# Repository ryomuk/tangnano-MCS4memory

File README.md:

# tangnano-MCS4memory
Memory system for Intel 4004 using Tang Nano 20K

This document is written mostly in Japanese.
If necessary, please use a translation service such as DeepL (I recommend this) or Google.

## 概要
[emu8080on4004](https://github.com/ryomuk/emu8080on4004)を動作させるための4004実験ボード(Rev.2.1)の「4004以外の部分」(主にメモリシステム)をTang Nano 20K に実装しました．
これにより，DigikeyやMouserで入手可能な部品とTangNano20KだけでIntel4004を動作させることができます．

## ボードの構成

部品のほとんどはレベル変換用IC(15V←→3.3V, 15Vクロックドライバ, UART用5V耐圧バッファ)です．

## Tang Nano 20Kに実装したもの
- 4002 x 4個 (data ram, 出力ポート)．出力ポートのLEDはRAM0の4個のみ．
- 4289 のプログラムメモリへのアクセス機能(ポート機能は未実装)
- プログラム領域のROM (4KB)
- プログラム領域のRAM (256byte x 256バンク = 64KB)
- 2相クロックジェネレータ

Rev.2.1ボードにおける下記の赤枠の部分がTangNano20Kに実装されています．

## 電源について
一般に，4004の回路は「VSS=-15V, VDD=0V(GND)」もしくは，「VSS=-10V, VDD=+5V, GND=0V」で設計されることが多いですが，3.3VCMOSへのレベル変換を考えた場合，
「VSS=+15V, VDD=0V(GND)」とした方が扱いやすそうだったのでそのようにしています．
(ちなみに，15V系CMOSはVSSとVDDは4004と逆で「VSS=0V(GND)，VDD=+15V」です．)
- +15Vが必要なのは4004とクロック用バッファだけで，消費電流は40mA(電力0.6W)程度なので，5V→15V,1WのDC/DCコンバータの(RECOM, ROE0515S)で生成しています．
- 外部から供給する電源は5Vのみで，消費電流はTangNano(100mA程度)とあわせて250mA程度です．いわゆる普通の5V USB電源でも動作します．

## 4004実験ボード(Rev.2.1)との互換性について
- ソフトウェアはバイナリレベルで互換性があるはずです．
- 4002の出力ポートのLED(計16個)は，RAM0の4個だけTangNanoのオンボードLEDとして実装されています．
- UARTは74HC4050経由にしたので，3.3V, 5Vの両方に対応しているはずです．(動作確認済なのは5Vのみ)

## ブログ
関連する情報が書いてあるかも．
- [Intel 4004 関連記事の目次@ブログの練習](https://blog.goo.ne.jp/tk-80/e/3fa1e2972737c7b7d1b83f4e7bd648a2)

## 更新履歴
- 2023/6/14: 初版公開

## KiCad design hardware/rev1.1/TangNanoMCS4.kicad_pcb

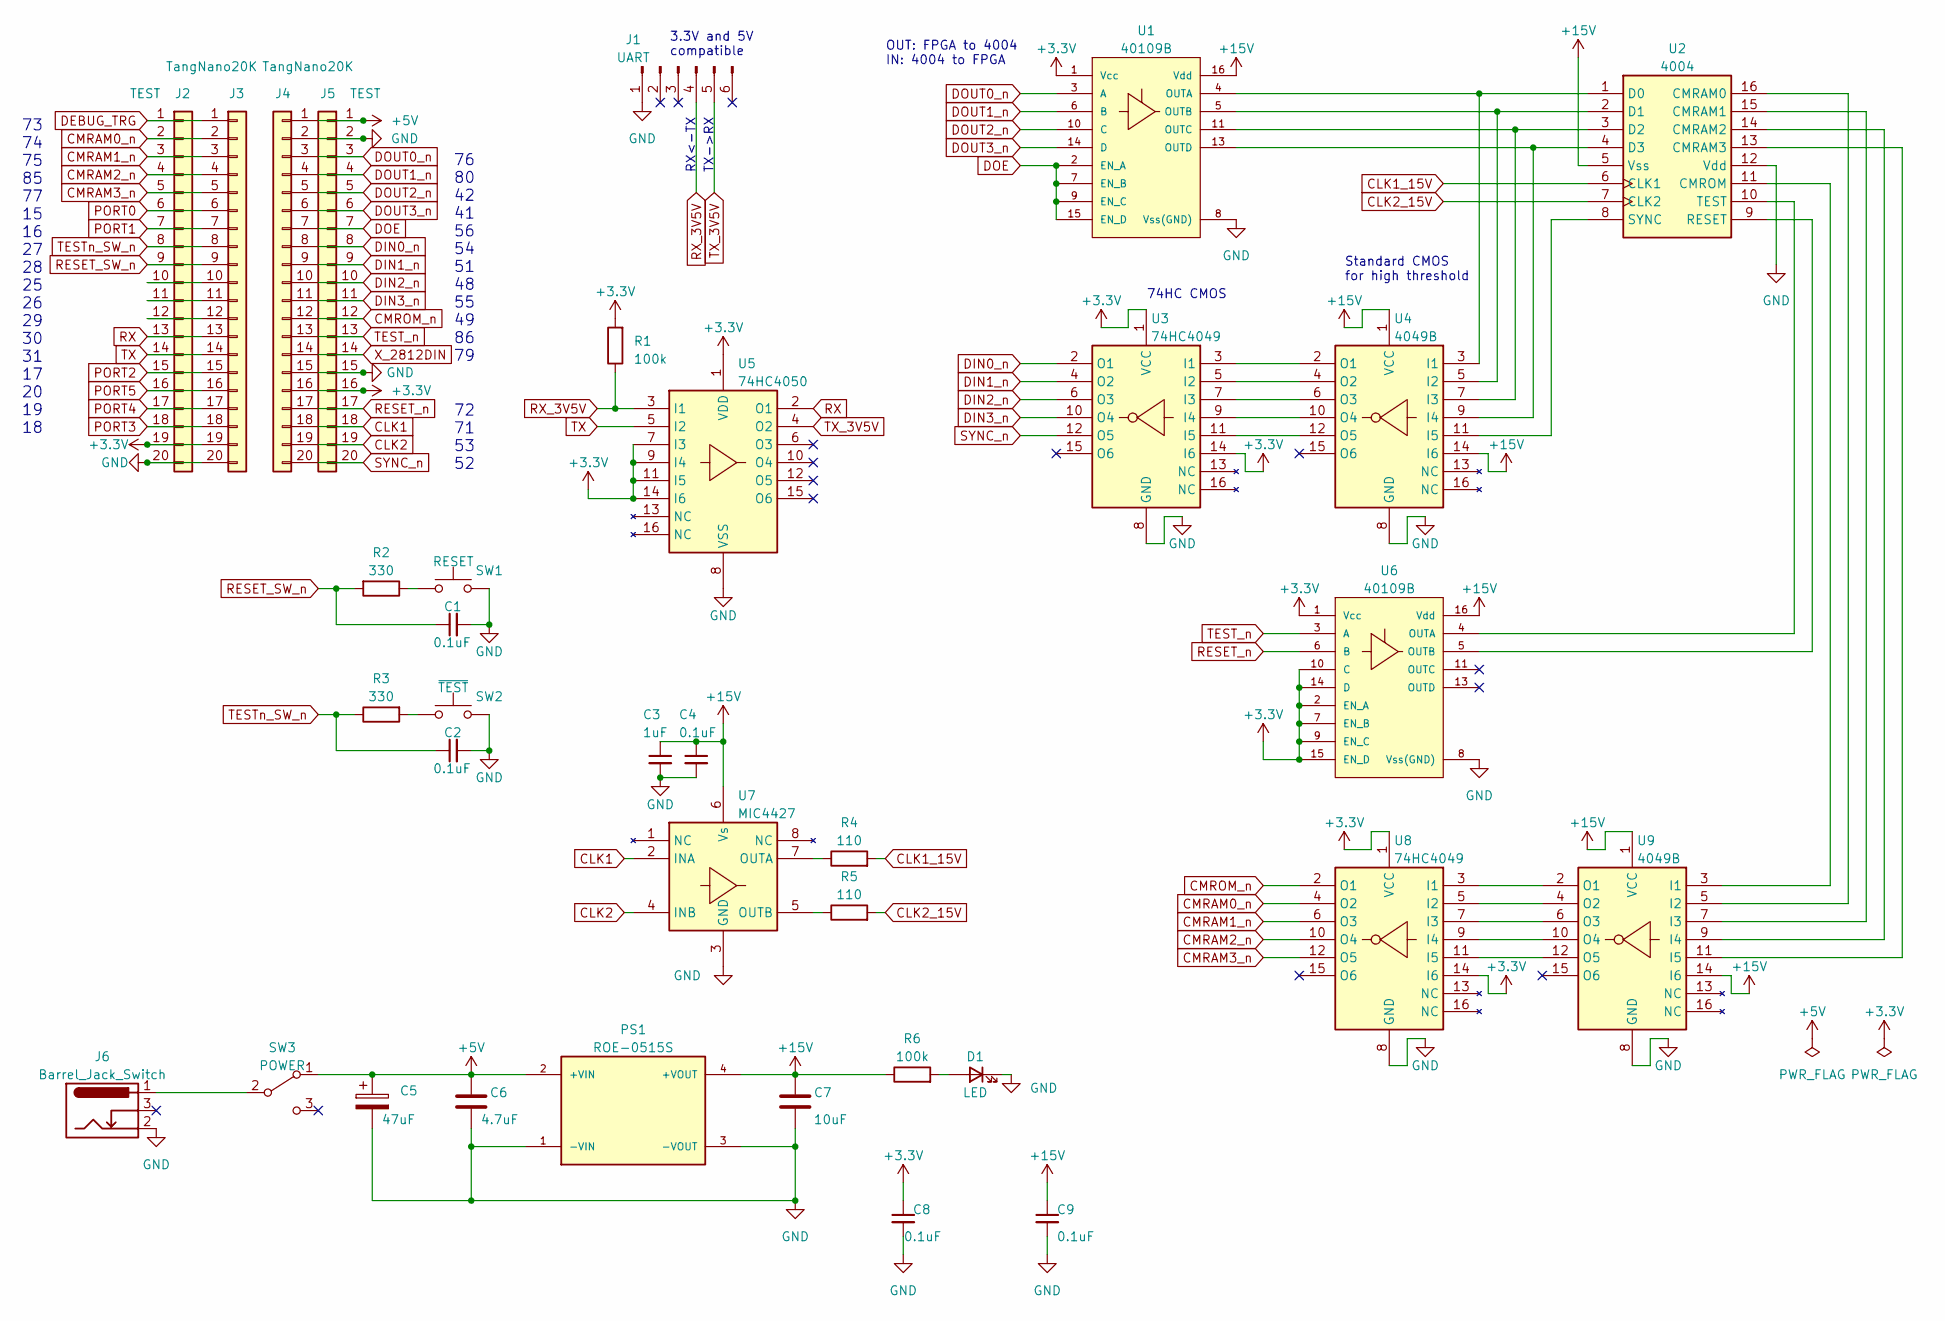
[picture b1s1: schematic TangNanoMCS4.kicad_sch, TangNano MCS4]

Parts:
C1, C2, C4, C8, C9: 0.1uF; C_Disc_D4.3mm_W1.9mm_P5.00mm
C3: 1uF; C_Disc_D4.3mm_W1.9mm_P5.00mm
C5: 47uF; CP_Radial_D6.3mm_P2.50mm
C6: 4.7uF; C_Disc_D4.7mm_W2.5mm_P5.00mm
C7: 10uF; C_Disc_D4.7mm_W2.5mm_P5.00mm
D1: LED; LED_D3.0mm
J1: UART; PinHeader_1x06_P2.54mm_Horizontal
J2, J5: TEST; PinSocket_1x20_P2.54mm_Vertical
J3, J4: TangNano20K; PinSocket_1x20_P2.54mm_Vertical
J6: Barrel_Jack_Switch; BarrelJack_Horizontal
PS1: ROE-0515S; CONV_ROE-0515S; PARTREV 5
R1, R6: 100k; R_Axial_DIN0207_L6.3mm_D2.5mm_P7.62mm_Horizontal
R2, R3: 330; R_Axial_DIN0207_L6.3mm_D2.5mm_P7.62mm_Horizontal
R4, R5: 110; R_Axial_DIN0207_L6.3mm_D2.5mm_P7.62mm_Horizontal
SW1: RESET; SW_PUSH_6mm_H4.3mm
SW2: ~{TEST}; SW_PUSH_6mm_H4.3mm
SW3: POWER; SW_SPDT_Toggle_with_mount
U1, U6: 40109B; DIP-16_W7.62mm
U2: 4004; DIP_Socket-16_W4.3_W5.08_W7.62_W10.16_W10.9_3M_216-3340-00-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
U3, U8: 74HC4049; DIP-16_W7.62mm
U4, U9: 4049B; DIP-16_W7.62mm
U5: 74HC4050; DIP-16_W7.62mm
U7: MIC4427; DIP-8_W7.62mm

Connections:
+3.3V: C8.1, J2.19, J3.19, J4.16, J5.16, R1.2, U1.1 (Vcc), U3.1 (VCC), U3.14 (I6), U5.1 (VDD), U5.7 (I3), U5.9 (I4), U5.11 (I5), U5.14 (I6), U6.1 (Vcc), U6.2 (EN_A), U6.7 (EN_B), U6.9 (EN_C), U6.10 (C), U6.14 (D), U6.15 (EN_D), U8.1 (VCC), U8.14 (I6)
+5V: C5.1, C6.1, J4.1, J5.1, PS1.2 (+VIN), SW3.1 (A)
+15V: C3.1, C4.1, C7.1, C9.1, PS1.4 (+VOUT), R6.1, U1.16 (Vdd), U2.5 (Vss), U4.1 (VCC), U4.14 (I6), U6.16 (Vdd), U7.6 (Vs), U9.1 (VCC), U9.14 (I6)
CLK1: J4.18, J5.18, U7.2 (INA)
CLK1_15V: R4.2, U2.6 (CLK1)
CLK2: J4.19, J5.19, U7.4 (INB)
CLK2_15V: R5.2, U2.7 (CLK2)
CMRAM0_n: J2.2, J3.2, U8.4 (O2)
CMRAM1_n: J2.3, J3.3, U8.6 (O3)
CMRAM2_n: J2.4, J3.4, U8.10 (O4)
CMRAM3_n: J2.5, J3.5, U8.12 (O5)
CMROM_n: J4.12, J5.12, U8.2 (O1)
DEBUG_TRG: J2.1, J3.1
DIN0_n: J4.8, J5.8, U3.2 (O1)
DIN1_n: J4.9, J5.9, U3.4 (O2)
DIN2_n: J4.10, J5.10, U3.6 (O3)
DIN3_n: J4.11, J5.11, U3.10 (O4)
DOE: J4.7, J5.7, U1.2 (EN_A), U1.7 (EN_B), U1.9 (EN_C), U1.15 (EN_D)
DOUT0_n: J4.3, J5.3, U1.3 (A)
DOUT1_n: J4.4, J5.4, U1.6 (B)
DOUT2_n: J4.5, J5.5, U1.10 (C)
DOUT3_n: J4.6, J5.6, U1.14 (D)
GND: C1.2, C2.2, C3.2, C4.2, C5.2, C6.2, C7.2, C8.2, C9.2, D1.1 (K), J1.1, J2.20, J3.20, J4.2, J4.15, J5.2, J5.15, J6.2, PS1.1 (-VIN), PS1.3 (-VOUT), SW1.2, SW2.2, U1.8 (Vss(GND)), U2.12 (Vdd), U3.8 (GND), U4.8 (GND), U5.8 (VSS), U6.8 (Vss(GND)), U7.3 (GND), U8.8 (GND), U9.8 (GND)
unnamed: D1.2 (A), R6.2
unnamed: J2.10, J3.10
unnamed: J2.11, J3.11
unnamed: J2.12, J3.12
unnamed: R2.1, SW1.1
unnamed: R3.2, SW2.1
unnamed: J6.1, SW3.2 (B)
unnamed: U1.4 (OUTA), U2.1 (D0), U4.3 (I1)
unnamed: U1.5 (OUTB), U2.2 (D1), U4.5 (I2)
unnamed: U1.11 (OUTC), U2.3 (D2), U4.7 (I3)
unnamed: U1.13 (OUTD), U2.4 (D3), U4.9 (I4)
unnamed: U2.16 (CMRAM0), U9.5 (I2)
unnamed: U2.15 (CMRAM1), U9.7 (I3)
unnamed: U2.14 (CMRAM2), U9.9 (I4)
unnamed: U2.13 (CMRAM3), U9.11 (I5)
unnamed: U2.11 (CMROM), U9.3 (I1)
unnamed: U2.9 (RESET), U6.5 (OUTB)
unnamed: U2.8 (SYNC), U4.11 (I5)
unnamed: U2.10 (TEST), U6.4 (OUTA)
unnamed: U3.3 (I1), U4.2 (O1)
unnamed: U3.5 (I2), U4.4 (O2)
unnamed: U3.7 (I3), U4.6 (O3)
unnamed: U3.9 (I4), U4.10 (O4)
unnamed: U3.11 (I5), U4.12 (O5)
unnamed: R4.1, U7.7 (OUTA)
unnamed: R5.1, U7.5 (OUTB)
unnamed: U8.3 (I1), U9.2 (O1)
unnamed: U8.5 (I2), U9.4 (O2)
unnamed: U8.7 (I3), U9.6 (O3)
unnamed: U8.9 (I4), U9.10 (O4)
unnamed: U8.11 (I5), U9.12 (O5)
PORT0: J2.6, J3.6
PORT1: J2.7, J3.7
PORT2: J2.15, J3.15
PORT3: J2.18, J3.18
PORT4: J2.17, J3.17
PORT5: J2.16, J3.16
RESET_SW_n: C1.1, J2.9, J3.9, R2.2
RESET_n: J4.17, J5.17, U6.6 (B)
RX: J2.13, J3.13, U5.2 (O1)
RX_3V5V: J1.4, R1.1, U5.3 (I1)
SYNC_n: J4.20, J5.20, U3.12 (O5)
TEST_n: J4.13, J5.13, U6.3 (A)
TESTn_SW_n: C2.1, J2.8, J3.8, R3.1
TX: J2.14, J3.14, U5.5 (I2)
TX_3V5V: J1.5, U5.4 (O2)
X_2812DIN: J4.14, J5.14

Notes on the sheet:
Standard CMOS for high threshold
OUT: FPGA to 4004 IN: 4004 to FPGA
74HC CMOS
3.3V and 5V compatible
TX->RX
76 80 42 41 56 54 51 48 55 49 86 79
RX<-TX
72 71 53 52
73 74 75 85 77 15 16 27 28 25 26 29 30 31 17 20 19 18

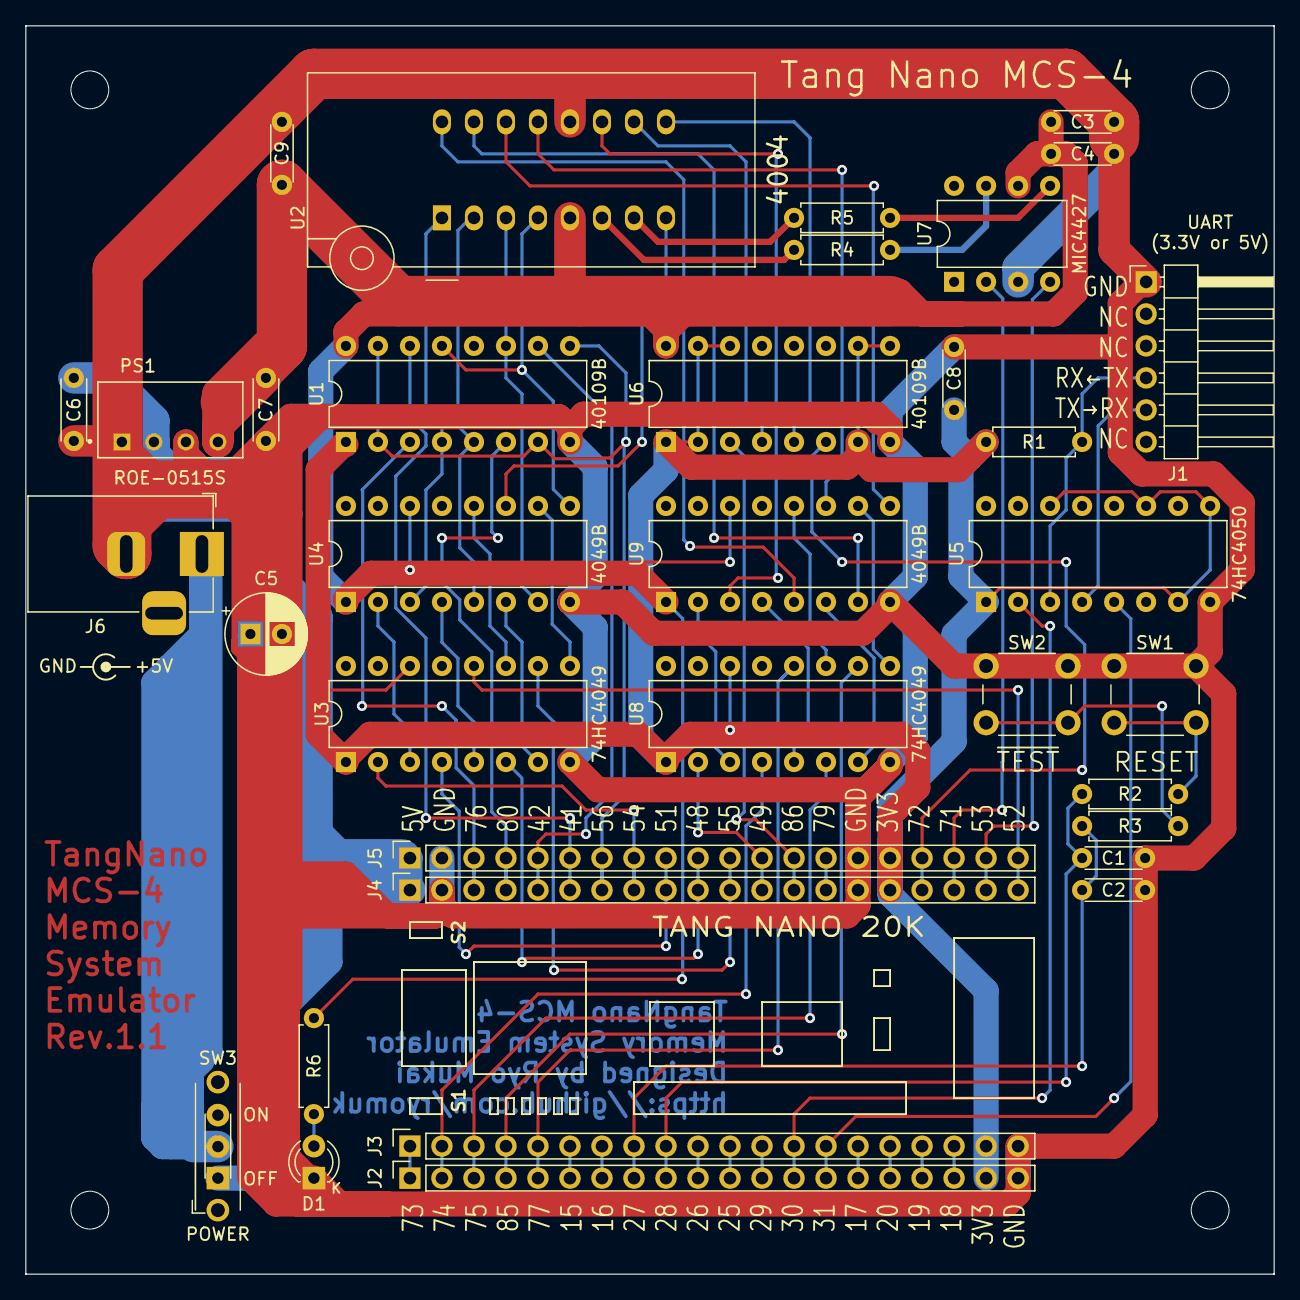
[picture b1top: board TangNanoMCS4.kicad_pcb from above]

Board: 2 copper layers, 99.1 x 99.1 mm, 35 parts (0 on the bottom side), 70 nets.

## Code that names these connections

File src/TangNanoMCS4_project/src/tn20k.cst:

IO_LOC  "led[5]"     20; IO_PORT "led[5]" PULL_MODE=UP DRIVE=8;
IO_LOC  "led[4]"     19; IO_PORT "led[4]" PULL_MODE=UP DRIVE=8;
IO_LOC  "led[3]"     18; IO_PORT "led[3]" PULL_MODE=UP DRIVE=8;
IO_LOC  "led[2]"     17; IO_PORT "led[2]" PULL_MODE=UP DRIVE=8;
IO_LOC  "led[1]"     16; IO_PORT "led[1]" PULL_MODE=UP DRIVE=8;
IO_LOC  "led[0]"     15; IO_PORT "led[0]" PULL_MODE=UP DRIVE=8;
IO_LOC  "ws2812"     79; IO_PORT "ws2812" DRIVE=8; // RGB LED
IO_LOC  "sw1"        88;
IO_LOC  "sw2"        87;
IO_LOC  "sys_clk"     4; IO_PORT "sys_clk" PULL_MODE=UP;

IO_LOC  "debug_trg"  73; IO_PORT "debug_trg" DRIVE=8;
IO_LOC  "cmram_n[0]" 74;
IO_LOC  "cmram_n[1]" 75;
IO_LOC  "cmram_n[2]" 85;
IO_LOC  "cmram_n[3]" 77;
// LED0 15
// LED1 16
IO_LOC  "testn_sw_n" 27; IO_PORT "testn_sw_n" PULL_MODE=UP;
IO_LOC  "reset_sw_n" 28; IO_PORT "reset_sw_n" PULL_MODE=UP;
// 26
// 25
// 29
IO_LOC  "rx"         30;
IO_LOC  "tx"         31; IO_PORT "tx" DRIVE=8;

IO_LOC  "dout_n[0]"  76; IO_PORT "dout_n[0]" DRIVE=8;
IO_LOC  "dout_n[1]"  80; IO_PORT "dout_n[1]" DRIVE=8;
IO_LOC  "dout_n[2]"  42; IO_PORT "dout_n[2]" DRIVE=8;
IO_LOC  "dout_n[3]"  41; IO_PORT "dout_n[3]" DRIVE=8;
IO_LOC  "doe"        56; IO_PORT "doe" DRIVE=8;
IO_LOC  "din_n[0]"   54;
IO_LOC  "din_n[1]"   51;
IO_LOC  "din_n[2]"   48;
IO_LOC  "din_n[3]"   55;
IO_LOC  "cmrom_n"    49;
IO_LOC  "test_n"     86; IO_PORT "test_n"  DRIVE=8;

IO_LOC  "reset_n"    72; IO_PORT "reset_n" DRIVE=8;
IO_LOC  "clk1"       71; IO_PORT "clk1" DRIVE=8;
IO_LOC  "clk2"       53; IO_PORT "clk2" DRIVE=8;
IO_LOC  "sync_n"     52;
